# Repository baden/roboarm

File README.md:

## Налаштування оточення

```bash
uv venv --python 3.12
source .venv/bin/activate
uv pip install matplotlib
uv pip install shapely
```

## Візуалізація

```bash
python ./test1.py
```

```bash
python ./pyplot_cycloid1.py
```

## Друге коліно.

Шось позаписую.
Зібрано прототип на базі

Шо я бачу. Шо 1:23 явно для 3Д друку - це перебір.
Зміщення +-1.0 замало, бажано раза в півтора підняти.

- зовнішнього підшипника 52х40х7
- внутрішнього підшипника спочатку на 8х22х7, потім замінено на 10х19х5

Шо я бачу.
Внутрішній треба спробувати всунути 15х24х5, для зміцнення валу

## База

Базу пропоную проєктувати на базі автомобільної ступіци.
Мені здається шо це може бути найпростіший, та мабуть найдешевний варіант.
Треба шоб конструкція витримувала навантаження на ізлом, мала б надійне кріплення до кузова.

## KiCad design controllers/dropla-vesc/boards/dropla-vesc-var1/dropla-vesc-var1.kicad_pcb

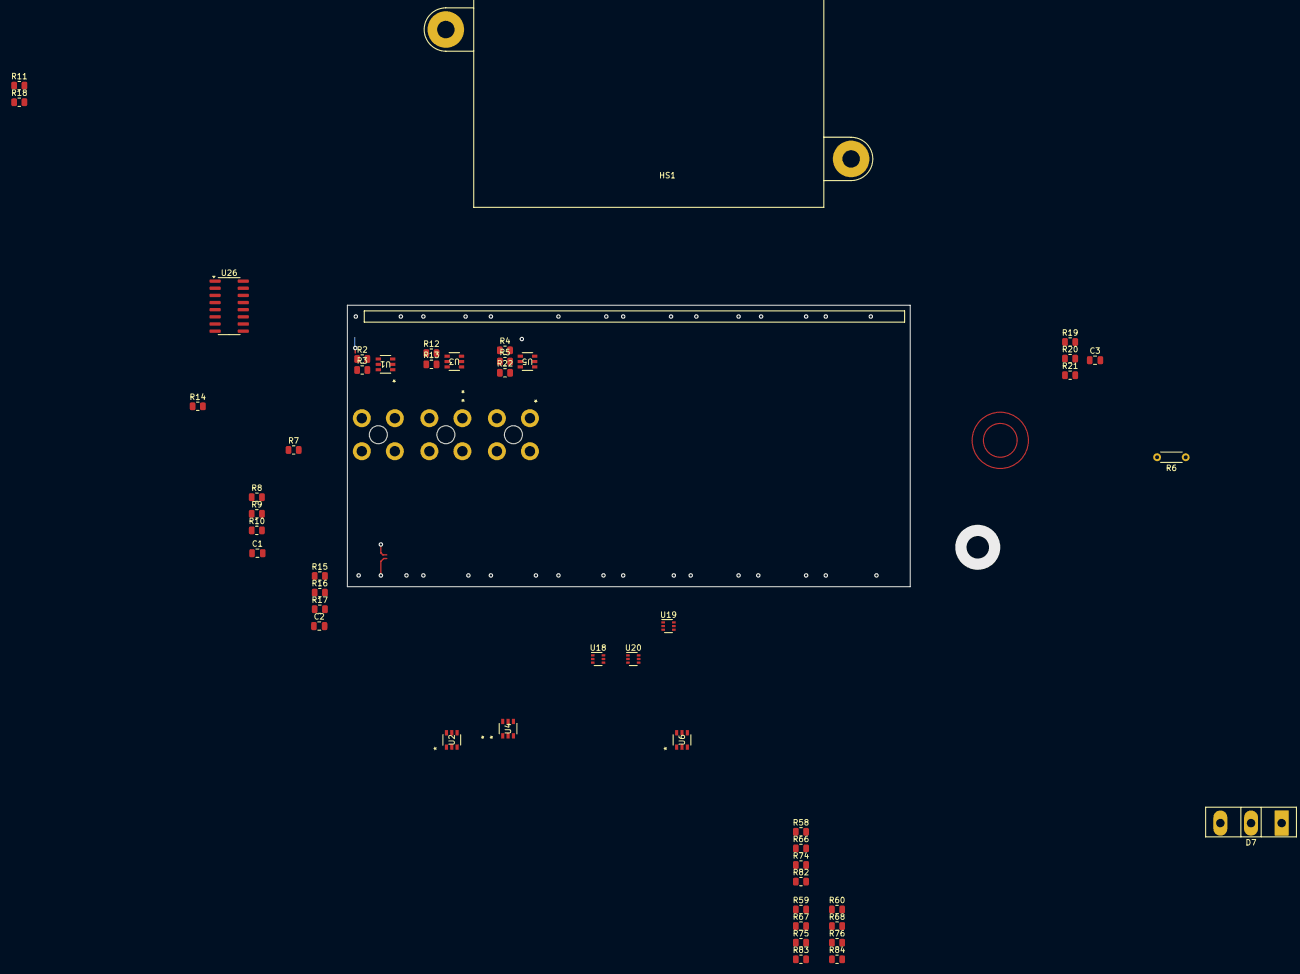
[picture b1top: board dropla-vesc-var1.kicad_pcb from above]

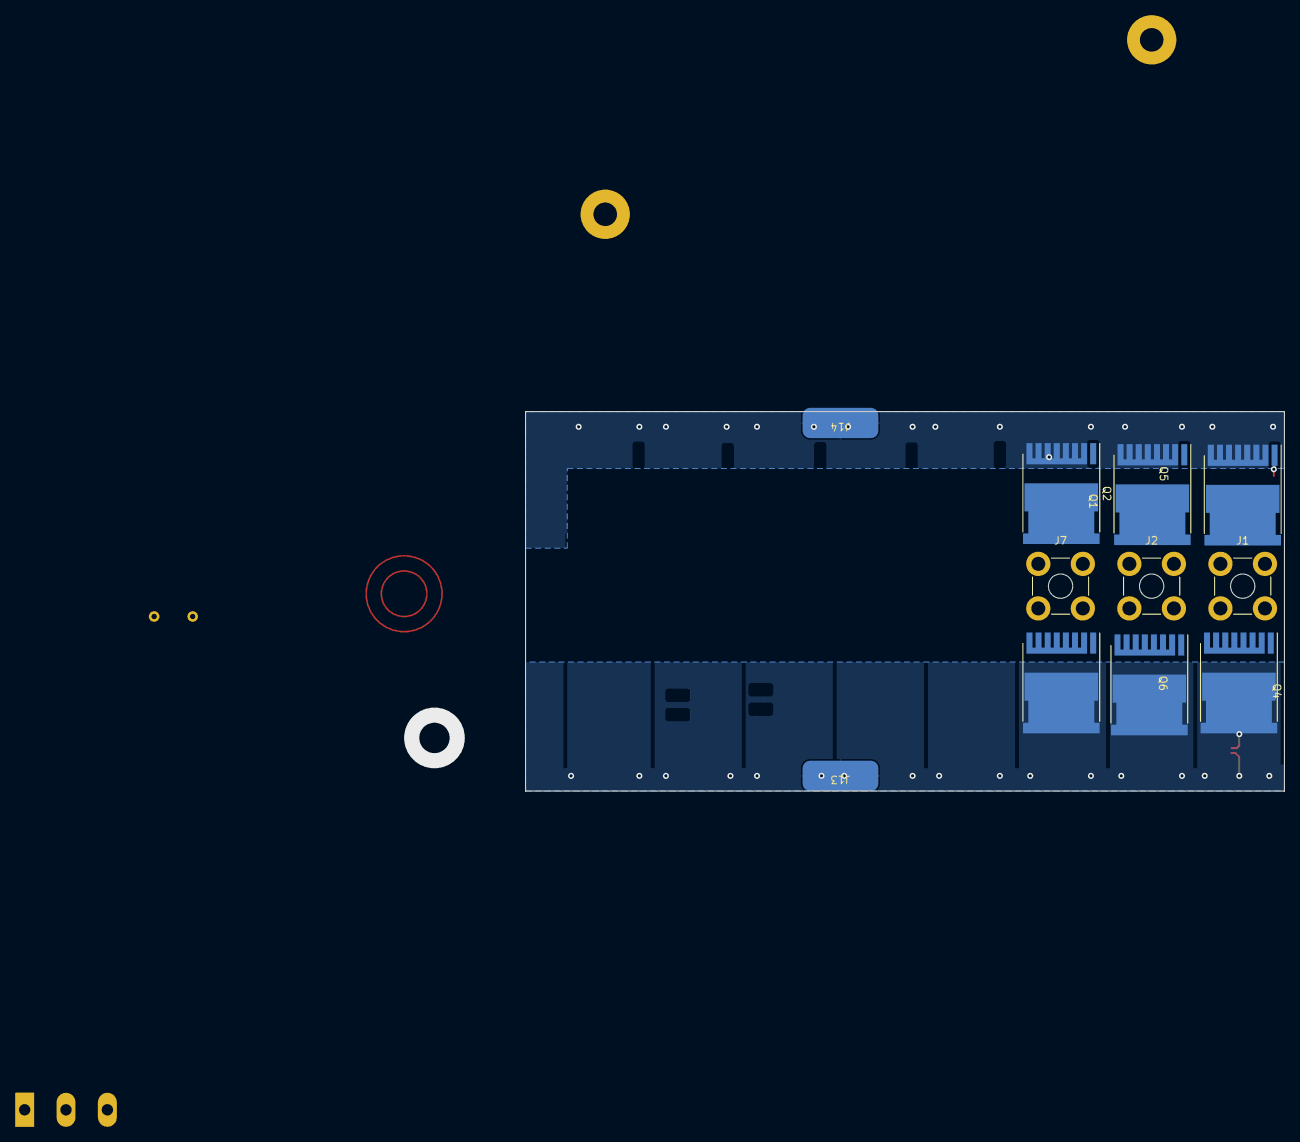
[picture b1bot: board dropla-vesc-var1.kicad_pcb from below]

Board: 2 copper layers, 100.0 x 50.0 mm, 59 parts (11 on the bottom side), 44 nets.

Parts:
C1, C2, C3: C; C_0805_2012Metric
D7: FEP30JP-E3/45; TO-247-3_Vertical
HS1: Heatsink; Heatsink_62x40mm_2xFixation3mm
J1, J2, J7: Screw_Terminal_01x01; Wuerth_REDCUBE-THR_WP-THRBU_74650073_THR
J13, J14: Screw_Terminal_01x01; copper_p_plate
Q1, Q2, Q3, Q4, Q5, Q6: IRFP4110PBF; Infineon_PG-HSOF-8-1
R2, R4, R7, R12, R14, R19: 10; R_0805_2012Metric
R3, R5, R8, R13, R15, R20: 47; R_0805_2012Metric
R6: 1k; R_Axial_DIN0204_L3.6mm_D1.6mm_P5.08mm_Horizontal
R9, R10, R11, R16, R17, R18, R21, R22, R58, R59, R60, R66, R67, R68, R74, R75, R76, R82, R83, R84: 10k; R_0805_2012Metric
U1, U2, U3, U4, U5, U6: 1EDN6550BXTSA1; PG-SOT23-6_INF
U18, U19, U20: NCS211; SOT-363_SC-70-6
U26: CH32V003AxMx; SOP-16_3.9x9.9mm_P1.27mm

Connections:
12V: U2.4 (VDD), U4.4 (VDD), U6.4 (VDD), U18.3 (Vs), U19.3 (Vs), U20.3 (Vs)
+36V: J14.1, Q1.2 (D), Q2.2 (D), Q5.2 (D)
/P1A: C1.2, J1.1, Q1.3 (S), Q4.2 (D), R10.2, U1.2 (GND)
/P1B: C2.2, J2.1, Q5.3 (S), Q6.2 (D), R17.2, U3.2 (GND)
/P2A: C3.2, J7.1, Q2.3 (S), Q3.2 (D), R22.2, U5.2 (GND)
/SCL: R18.1, U26.2 (PC2)
/SDA: R11.1, U26.1 (PC1)
/driver 1A/PWM1: R58.1, R82.1
/driver 1A/PWM2: R66.1, R74.1
/driver 1B/PWM1: R59.1, R83.1
/driver 1B/PWM2: R67.1, R75.1
/driver 2A/PWM1: R60.1, R84.1
/driver 2A/PWM2: R68.1, R76.1
GND: J13.1, Q3.3 (S), Q4.3 (S), Q6.3 (S), R9.2, R16.2, R21.2, U2.2 (GND), U4.2 (GND), U6.2 (GND), U18.2 (GND), U18.4 (+IN), U18.5 (-IN), U19.2 (GND), U19.4 (+IN), U19.5 (-IN), U20.2 (GND), U20.4 (+IN), U20.5 (-IN)
unnamed: C1.1, R2.2, U1.4 (VDD), U1.6 (OUT_SNK)
unnamed: C2.1, R12.2, U3.4 (VDD), U3.6 (OUT_SNK)
unnamed: C3.1, R4.2, U5.4 (VDD), U5.6 (OUT_SNK)
unnamed: Q1.1 (G), R2.1, R3.1, R10.1
unnamed: Q2.1 (G), R4.1, R5.1, R22.1
unnamed: Q3.1 (G), R19.1, R20.1, R21.1
unnamed: Q4.1 (G), R7.1, R8.1, R9.1
unnamed: Q5.1 (G), R12.1, R13.1, R17.1
unnamed: Q6.1 (G), R14.1, R15.1, R16.1
unnamed: R66.2, U1.3 (IN+)
unnamed: R58.2, U1.1 (IN-)
unnamed: R3.2, U1.5 (OUT_SRC)
unnamed: R82.2, U2.3 (IN+)
unnamed: R74.2, U2.1 (IN-)
unnamed: R7.2, U2.6 (OUT_SNK)
unnamed: R8.2, U2.5 (OUT_SRC)
unnamed: R67.2, U3.3 (IN+)
unnamed: R59.2, U3.1 (IN-)
unnamed: R13.2, U3.5 (OUT_SRC)
unnamed: R83.2, U4.3 (IN+)
unnamed: R75.2, U4.1 (IN-)
unnamed: R14.2, U4.6 (OUT_SNK)
unnamed: R15.2, U4.5 (OUT_SRC)
unnamed: R68.2, U5.3 (IN+)
unnamed: R60.2, U5.1 (IN-)
unnamed: R5.2, U5.5 (OUT_SRC)
unnamed: R84.2, U6.3 (IN+)
unnamed: R76.2, U6.1 (IN-)
unnamed: R19.2, U6.6 (OUT_SNK)
unnamed: R20.2, U6.5 (OUT_SRC)

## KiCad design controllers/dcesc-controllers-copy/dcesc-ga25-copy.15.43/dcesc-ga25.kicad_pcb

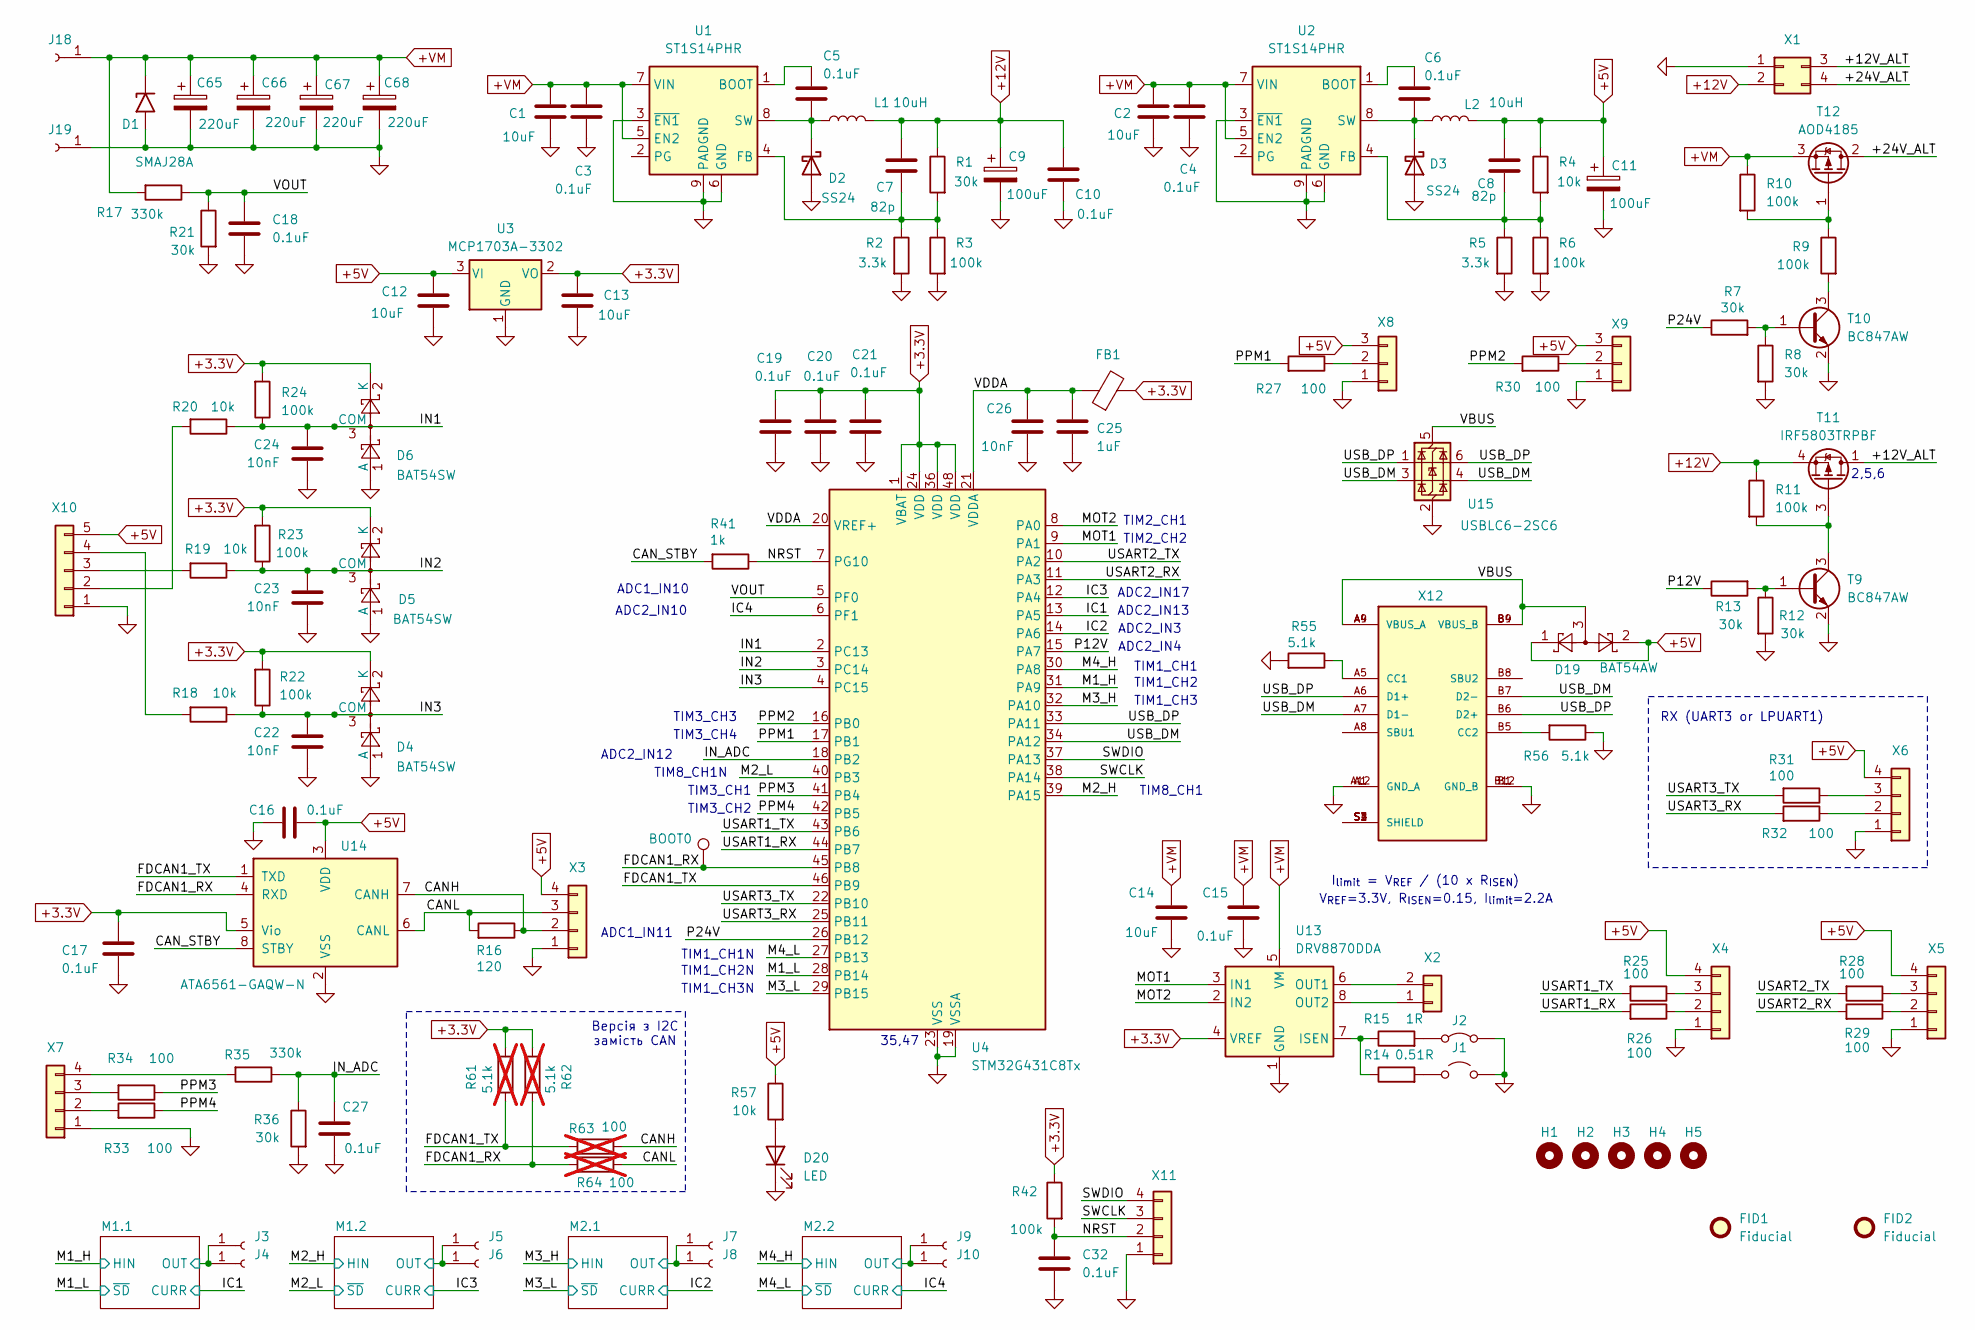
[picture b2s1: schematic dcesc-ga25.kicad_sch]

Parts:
C1, C2, C14: 10uF; C_1206_3216Metric
C3, C4, C5, C6, C10, C15, C16, C17, C18, C19, C20, C21, C27, C32: 0.1uF; C_0603_1608Metric
C7, C8: 82p; C_0603_1608Metric
C9: 100uF; CP_EIA-7343-15_Kemet-W
C11: 100uF; CP_EIA-3528-12_Kemet-T
C12, C13: 10uF; C_0805_2012Metric
C22, C23, C24, C26: 10nF; C_0603_1608Metric
C25: 1uF; C_0603_1608Metric
C65, C66, C67, C68: 220uF; CP_Radial_D10.0mm_P5.00mm
D1: SMAJ28A; D_SMA
D2, D3: SS24; D_SMA
D4, D5, D6: BAT54SW; SOT-323_SC-70
D19: BAT54AW; SOT-323_SC-70
D20: LED; LED_0805_2012Metric
FB1: FerriteBead; L_0603_1608Metric
FID1, FID2: Fiducial; Fiducial_1mm_Mask2mm
H1, H2, H3, H4, H5: MountingHole; MountingHole_3.2mm_M3
J1: Jumper_2_Open; SolderJumper-2_P1.3mm_Open_RoundedPad1.0x1.5mm
J2: Jumper_2_Bridged; SolderJumper-2_P1.3mm_Bridged_RoundedPad1.0x1.5mm
J3, J4, J5, J6, J7, J8, J9, J10: Conn_01x01_Socket; SolderWire-2.5sqmm_1x01_D2.4mm_OD4.4mm
J18, J19: Conn_01x01_Socket; SolderWire-6sqmm_1x01_D3.5mm_OD7mm
L1, L2: 10uH; Inductor_NR6028T100M
R1, R7, R8, R12, R13, R21, R36: 30k; R_0603_1608Metric
R2, R5: 3.3k; R_0603_1608Metric
R3, R6, R9, R10, R11, R22, R23, R24, R42: 100k; R_0603_1608Metric
R4, R18, R19, R20, R57: 10k; R_0603_1608Metric
R14: 0.51R; R_1206_3216Metric
R15: 1R; R_1206_3216Metric
R16: 120; R_0603_1608Metric
R17, R35: 330k; R_0603_1608Metric
R25, R26, R27, R28, R29, R30, R31, R32, R33, R34: 100; R_0603_1608Metric
R41: 1k; R_0603_1608Metric
R55, R56: 5.1k; R_0603_1608Metric
R61, R62: 5.1k; R_0603_1608Metric; not fitted
R63, R64: 100; R_0603_1608Metric; not fitted
T9, T10: BC847AW; SOT-323_SC-70
T11: IRF5803TRPBF; TSOP-6_1.65x3.05mm_P0.95mm
T12: AOD4185; TO-252-2
TP1: BOOT0; TestPoint_Pad_1.0x1.0mm
U1, U2: ST1S14PHR; TI_SO-PowerPAD-8
U3: MCP1703A-3302; MCP1703; MPN MCP1703T-3302E/CB
U4: STM32G431C8Tx; LQFP-48_7x7mm_P0.5mm
U13: DRV8870DDA; Texas_HTSOP-8-1EP_3.9x4.9mm_P1.27mm_EP2.95x4.9mm_Mask2.4x3.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
U14: ATA6561-GAQW-N; SOIC-8_3.9x4.9mm_P1.27mm
U15: USBLC6-2SC6; SOT-23-6
X1: Conn_02x02_Top_Bottom; Molex_Micro-Fit_3.0_43045-0412_2x02_P3.00mm_Vertical
X2: Conn_01x03; JST_XH_B2B-XH-AM_1x02_P2.50mm_Vertical
X3, X4, X5, X6, X7, X11: Conn_01x03; JST_ZH_B4B-ZR_1x04_P1.50mm_Vertical
X8, X9: Conn_01x03; JST_ZH_B3B-ZR_1x03_P1.50mm_Vertical
X10: Conn_01x03; JST_ZH_B5B-ZR_1x05_P1.50mm_Vertical
X12: USB4120-03-C_REVA; GCT_USB4120-03-C_REVA; PARTREV A

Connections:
+3.3V: C13.1, C17.1, C19.1, C20.1, C21.1, D4.2 (K), D5.2 (K), D6.2 (K), FB1.2, R22.2, R23.2, R24.2, R42.1, R61.1, R62.1, U3.2 (VO), U4.1 (VBAT), U4.24 (VDD), U4.36 (VDD), U4.48 (VDD), U13.4 (VREF), U14.5 (Vio); also elsewhere on the board
+5V: C8.1, C11.1, C12.1, C16.1, D19.1, D19.2, L2.2, R4.1, R57.1, U3.3 (VI), U14.3 (VDD), X3.4, X4.4, X5.4, X6.4, X8.3, X9.3, X10.5
+12V: C7.1, C9.1, C10.1, L1.2, R1.1, R11.1, T11.4 (S), X1.2; also elsewhere on the board
+VM: C1.1, C2.1, C3.1, C4.1, C14.1, C15.1, C65.1, C66.1, C67.1, C68.1, D1.1 (A1), J18.1, R10.1, R17.2, T12.3 (S), U1.5 (EN2), U1.7 (VIN), U2.5 (EN2), U2.7 (VIN), U13.5 (VM); also elsewhere on the board
/+12V_ALT: T11.1 (D), T11.2 (D), T11.5 (D), T11.6 (D), X1.3
/+24V_ALT: T12.2 (D), X1.4
/CANH: R16.1, R63.2, U14.7 (CANH), X3.2
/CANL: R16.2, R64.1, U14.6 (CANL), X3.3
/CAN_STBY: R41.2, U14.8 (STBY)
/FDCAN1_RX: R62.2, R64.2, TP1.1, U4.45 (PB8), U14.4 (RXD)
/FDCAN1_TX: R61.2, R63.1, U4.46 (PB9), U14.1 (TXD)
/IC1: U4.13 (PA5); also elsewhere on the board
/IC2: U4.14 (PA6); also elsewhere on the board
/IC3: U4.12 (PA4); also elsewhere on the board
/IC4: U4.6 (PF1); also elsewhere on the board
/IN1: C24.1, D6.3 (COM), R20.1, R24.1, U4.2 (PC13)
/IN2: C23.1, D5.3 (COM), R19.1, R23.1, U4.3 (PC14)
/IN3: C22.1, D4.3 (COM), R18.1, R22.1, U4.4 (PC15)
/IN_ADC: C27.1, R35.1, R36.1, U4.18 (PB2)
/M1.1/OUT: J3.1, J4.1; also elsewhere on the board
/M1.2/OUT: J5.1, J6.1; also elsewhere on the board
/M1_H: U4.31 (PA9); also elsewhere on the board
/M1_L: U4.28 (PB14); also elsewhere on the board
/M2.1/OUT: J7.1, J8.1; also elsewhere on the board
/M2.2/OUT: J9.1, J10.1; also elsewhere on the board
/M2_H: U4.39 (PA15); also elsewhere on the board
/M2_L: U4.40 (PB3); also elsewhere on the board
/M3_H: U4.32 (PA10); also elsewhere on the board
/M3_L: U4.29 (PB15); also elsewhere on the board
/M4_H: U4.30 (PA8); also elsewhere on the board
/M4_L: U4.27 (PB13); also elsewhere on the board
/MOT1: U4.9 (PA1), U13.3 (IN1)
/MOT2: U4.8 (PA0), U13.2 (IN2)
/NRST: C32.1, R41.1, R42.2, U4.7 (PG10), X11.2
/P12V: R13.1, U4.15 (PA7)
/P24V: R7.1, U4.26 (PB12)
/PPM1: R27.2, U4.17 (PB1)
/PPM2: R30.2, U4.16 (PB0)
/PPM3: R34.1, U4.41 (PB4)
/PPM4: R33.1, U4.42 (PB5)
/SWCLK: U4.38 (PA14), X11.3
/SWDIO: U4.37 (PA13), X11.4
/USART1_RX: R26.2, U4.44 (PB7)
/USART1_TX: R25.2, U4.43 (PB6)
/USART2_RX: R29.2, U4.11 (PA3)
/USART2_TX: R28.2, U4.10 (PA2)
/USART3_RX: R32.2, U4.25 (PB11)
/USART3_TX: R31.2, U4.22 (PB10)
/USB_DM: U4.34 (PA12), U15.3 (I/O2), U15.4 (I/O2), X12.A7 (D1-), X12.B7 (D2-)
/USB_DP: U4.33 (PA11), U15.1 (I/O1), U15.6 (I/O1), X12.A6 (D1+), X12.B6 (D2+)
/VBUS: D19.3, U15.5 (VBUS), X12.A4 (VBUS_A), X12.A9 (VBUS_A), X12.B4 (VBUS_B), X12.B9 (VBUS_B)
/VDDA: C25.1, C26.1, FB1.1, U4.20 (VREF+), U4.21 (VDDA)
/VOUT: C18.1, R17.1, R21.1, U4.5 (PF0)
GND: C1.2, C2.2, C3.2, C4.2, C9.2, C10.2, C11.2, C12.2, C13.2, C14.2, C15.2, C16.2, C17.2, C18.2, C19.2, C20.2, C21.2, C22.2, C23.2, C24.2, C25.2, C26.2, C27.2, C32.2, C65.2, C66.2, C67.2, C68.2, D1.2 (A2), D2.2 (A), D3.2 (A), D4.1 (A), D5.1 (A), D6.1 (A), D20.1 (K), J1.2 (B), J2.2 (B), J19.1, R2.2, R3.2, R5.2, R6.2, R8.2, R12.2, R21.2, R36.2, R55.2, R56.1, T9.2 (E), T10.2 (E), U1.3 (~EN1), U1.6 (GND), U1.9 (PADGND), U2.3 (~EN1), U2.6 (GND), U2.9 (PADGND), U3.1 (GND), U4.19 (VSSA), U4.23 (VSS), U4.35 (VSS), U4.47 (VSS), U13.1 (GND), U13.9 (GND), U14.2 (VSS), U15.2 (GND), X1.1, X3.1, X4.1, X5.1, X6.1, X7.1, X8.1, X9.1, X10.1, X11.1, X12.A1 (GND_A), X12.A12 (GND_A), X12.B1 (GND_B), X12.B12 (GND_B); also elsewhere on the board
unnamed: C5.2, D2.1 (K), L1.1, U1.8 (SW)
unnamed: C6.2, D3.1 (K), L2.1, U2.8 (SW)
unnamed: D20.2 (A), R57.2
unnamed: J1.1 (A), R14.2
unnamed: J2.1 (A), R15.2
unnamed: R12.1, R13.2, T9.1 (B)
unnamed: R7.2, R8.1, T10.1 (B)
unnamed: R9.2, T10.3 (C)
unnamed: R11.2, T9.3 (C), T11.3 (G)
unnamed: R9.1, R10.2, T12.1 (G)
unnamed: C5.1, U1.1 (BOOT)
unnamed: C7.2, R1.2, R2.1, R3.1, U1.4 (FB)
unnamed: C6.1, U2.1 (BOOT)
unnamed: C8.2, R4.2, R5.1, R6.1, U2.4 (FB)
unnamed: R14.1, R15.1, U13.7 (ISEN)
unnamed: U13.6 (OUT1), X2.2
unnamed: U13.8 (OUT2), X2.1
unnamed: R26.1, X4.2
unnamed: R25.1, X4.3
unnamed: R29.1, X5.2
unnamed: R28.1, X5.3
unnamed: R32.1, X6.2
unnamed: R31.1, X6.3
unnamed: R33.2, X7.2
unnamed: R34.2, X7.3
unnamed: R35.2, X7.4
unnamed: R27.1, X8.2
unnamed: R30.1, X9.2
unnamed: R20.2, X10.2
unnamed: R19.2, X10.3
unnamed: R18.2, X10.4
unnamed: R55.1, X12.A5 (CC1)
unnamed: R56.2, X12.B5 (CC2)
unnamed: X12.S1 (SHIELD), X12.S2 (SHIELD), X12.S3 (SHIELD), X12.S4 (SHIELD)

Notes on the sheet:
TIM1_CH2N
TIM1_CH2
TIM3_CH1
ADC2_IN13
Версія з I2C замість CAN
TIM1_CH1
2,5,6
ADC1_IN10
TIM8_CH1
TIM1_CH1N
TIM3_CH4
ADC2_IN12
TIM3_CH3
RX (UART3 or LPUART1)
ADC1_IN11
I_{limit} = V_{REF} / (10 x R_{ISEN})
TIM1_CH3
TIM1_CH3N
V_{REF}=3.3V, R_{ISEN}=0.15, I_{limit}=2.2A
ADC2_IN17
TIM8_CH1N
TIM3_CH2
ADC2_IN4
ADC2_IN3
TIM2_CH2
ADC2_IN10
35,47
TIM2_CH1

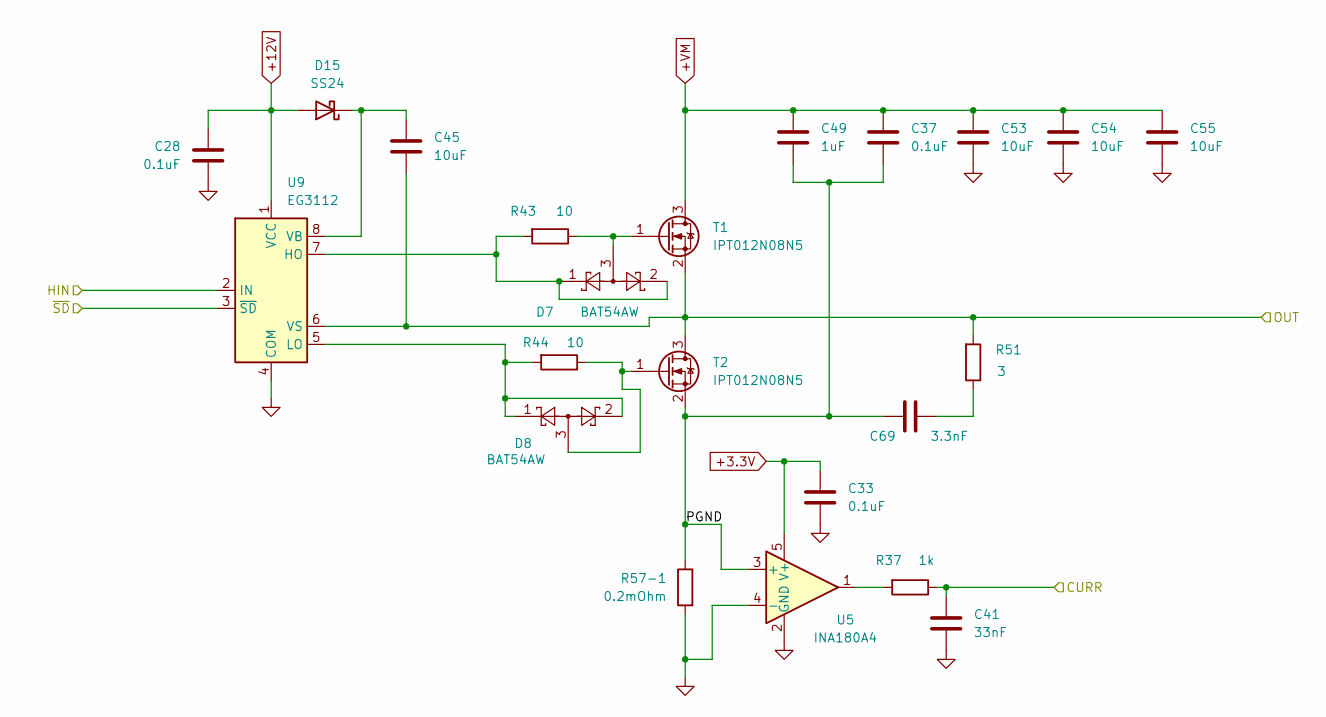
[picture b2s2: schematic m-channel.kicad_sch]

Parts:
C28, C33, C37: 0.1uF; C_0603_1608Metric
C41: 33nF; C_0603_1608Metric
C45: 10uF; C_0805_2012Metric
C49: 1uF; C_0805_2012Metric
C53, C54, C55: 10uF; C_1206_3216Metric
C69: 3.3nF; C_0603_1608Metric
D7, D8: BAT54AW; SOT-323_SC-70
D15: SS24; D_SMA
R37: 1k; R_0603_1608Metric
R43, R44: 10; R_0603_1608Metric
R51: 3; R_1206_3216Metric
R57-1: 0.2mOhm; R_SHUNT
T1, T2: IPT012N08N5; Infineon_PG-HSOF-8-1
U5: INA180A4; SOT-23-5
U9: EG3112; SOP-8_3.9x4.9mm_P1.27mm

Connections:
+3.3V: C33.1, U5.5 (V+); also elsewhere on the board
+12V: C28.1, D15.2 (A), U9.1 (VCC); also elsewhere on the board
+VM: C37.1, C49.1, C53.1, C54.1, C55.1, T1.3 (D); also elsewhere on the board
/IC1: C41.1, R37.1; also elsewhere on the board
/M1.1/OUT: C45.2, R51.2, T1.2 (S), T2.3 (D), U9.6 (VS); also elsewhere on the board
/M1.1/PGND: C37.2, C49.2, C69.2, R57-1.1, T2.2 (S), U5.3 (+)
/M1_H: U9.2 (IN); also elsewhere on the board
/M1_L: U9.3 (~SD); also elsewhere on the board
GND: C28.2, C33.2, C41.2, C53.2, C54.2, C55.2, R57-1.2, U5.2 (GND), U5.4 (-), U9.4 (COM); also elsewhere on the board
unnamed: C69.1, R51.1
unnamed: C45.1, D15.1 (K), U9.8 (VB)
unnamed: R37.2, U5.1
unnamed: D7.3, R43.1, T1.1 (G)
unnamed: D8.3, R44.1, T2.1 (G)
unnamed: D7.1, D7.2, R43.2, U9.7 (HO)
unnamed: D8.1, D8.2, R44.2, U9.5 (LO)

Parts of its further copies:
C29, C30, C31, C34, C35, C36, C38, C39, C40: 0.1uF; C_0603_1608Metric
C42, C43, C44: 33nF; C_0603_1608Metric
C46, C47, C48: 10uF; C_0805_2012Metric
C50, C51, C52: 1uF; C_0805_2012Metric
C56, C57, C58, C59, C60, C61, C62, C63, C64: 10uF; C_1206_3216Metric
C70, C71, C72: 3.3nF; C_0603_1608Metric
D9, D10, D11, D12, D13, D14: BAT54AW; SOT-323_SC-70
D16, D17, D18: SS24; D_SMA
R38, R39, R40: 1k; R_0603_1608Metric
R45, R46, R47, R48, R49, R50: 10; R_0603_1608Metric
R52, R53, R54: 3; R_1206_3216Metric
R58-1, R59-1, R60-1: 0.2mOhm; R_SHUNT
T3, T4, T5, T6, T7, T8: IPT012N08N5; Infineon_PG-HSOF-8-1
U6, U7, U8: INA180A4; SOT-23-5
U10, U11, U12: EG3112; SOP-8_3.9x4.9mm_P1.27mm

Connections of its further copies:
+3.3V: C34.1, C35.1, C36.1, U6.5 (V+), U7.5 (V+), U8.5 (V+); also elsewhere on the board
+12V: C29.1, C30.1, C31.1, D16.2 (A), D17.2 (A), D18.2 (A), U10.1 (VCC), U11.1 (VCC), U12.1 (VCC); also elsewhere on the board
+VM: C38.1, C39.1, C40.1, C50.1, C51.1, C52.1, C56.1, C57.1, C58.1, C59.1, C60.1, C61.1, C62.1, C63.1, C64.1, T3.3 (D), T5.3 (D), T7.3 (D); also elsewhere on the board
/IC2: C43.1, R39.1; also elsewhere on the board
/IC3: C42.1, R38.1; also elsewhere on the board
/IC4: C44.1, R40.1; also elsewhere on the board
/M1.2/OUT: C46.2, R52.2, T3.2 (S), T4.3 (D), U10.6 (VS); also elsewhere on the board
/M1.2/PGND: C38.2, C50.2, C70.2, R59-1.1, T4.2 (S), U6.3 (+)
/M2.1/OUT: C47.2, R53.2, T5.2 (S), T6.3 (D), U11.6 (VS); also elsewhere on the board
/M2.1/PGND: C39.2, C51.2, C71.2, R58-1.1, T6.2 (S), U7.3 (+)
/M2.2/OUT: C48.2, R54.2, T7.2 (S), T8.3 (D), U12.6 (VS); also elsewhere on the board
/M2.2/PGND: C40.2, C52.2, C72.2, R60-1.1, T8.2 (S), U8.3 (+)
/M2_H: U10.2 (IN); also elsewhere on the board
/M2_L: U10.3 (~SD); also elsewhere on the board
/M3_H: U11.2 (IN); also elsewhere on the board
/M3_L: U11.3 (~SD); also elsewhere on the board
/M4_H: U12.2 (IN); also elsewhere on the board
/M4_L: U12.3 (~SD); also elsewhere on the board
GND: C29.2, C30.2, C31.2, C34.2, C35.2, C36.2, C42.2, C43.2, C44.2, C56.2, C57.2, C58.2, C59.2, C60.2, C61.2, C62.2, C63.2, C64.2, R58-1.2, R59-1.2, R60-1.2, U6.2 (GND), U6.4 (-), U7.2 (GND), U7.4 (-), U8.2 (GND), U8.4 (-), U10.4 (COM), U11.4 (COM), U12.4 (COM); also elsewhere on the board
unnamed: C70.1, R52.1
unnamed: C71.1, R53.1
unnamed: C72.1, R54.1
unnamed: C46.1, D16.1 (K), U10.8 (VB)
unnamed: C47.1, D17.1 (K), U11.8 (VB)
unnamed: C48.1, D18.1 (K), U12.8 (VB)
unnamed: R38.2, U6.1
unnamed: R39.2, U7.1
unnamed: R40.2, U8.1
unnamed: D9.3, R45.1, T3.1 (G)
unnamed: D10.3, R46.1, T4.1 (G)
unnamed: D11.3, R47.1, T5.1 (G)
unnamed: D12.3, R48.1, T6.1 (G)
unnamed: D13.3, R49.1, T7.1 (G)
unnamed: D14.3, R50.1, T8.1 (G)
unnamed: D9.1, D9.2, R45.2, U10.7 (HO)
unnamed: D10.1, D10.2, R46.2, U10.5 (LO)
unnamed: D11.1, D11.2, R47.2, U11.7 (HO)
unnamed: D12.1, D12.2, R48.2, U11.5 (LO)
unnamed: D13.1, D13.2, R49.2, U12.7 (HO)
unnamed: D14.1, D14.2, R50.2, U12.5 (LO)

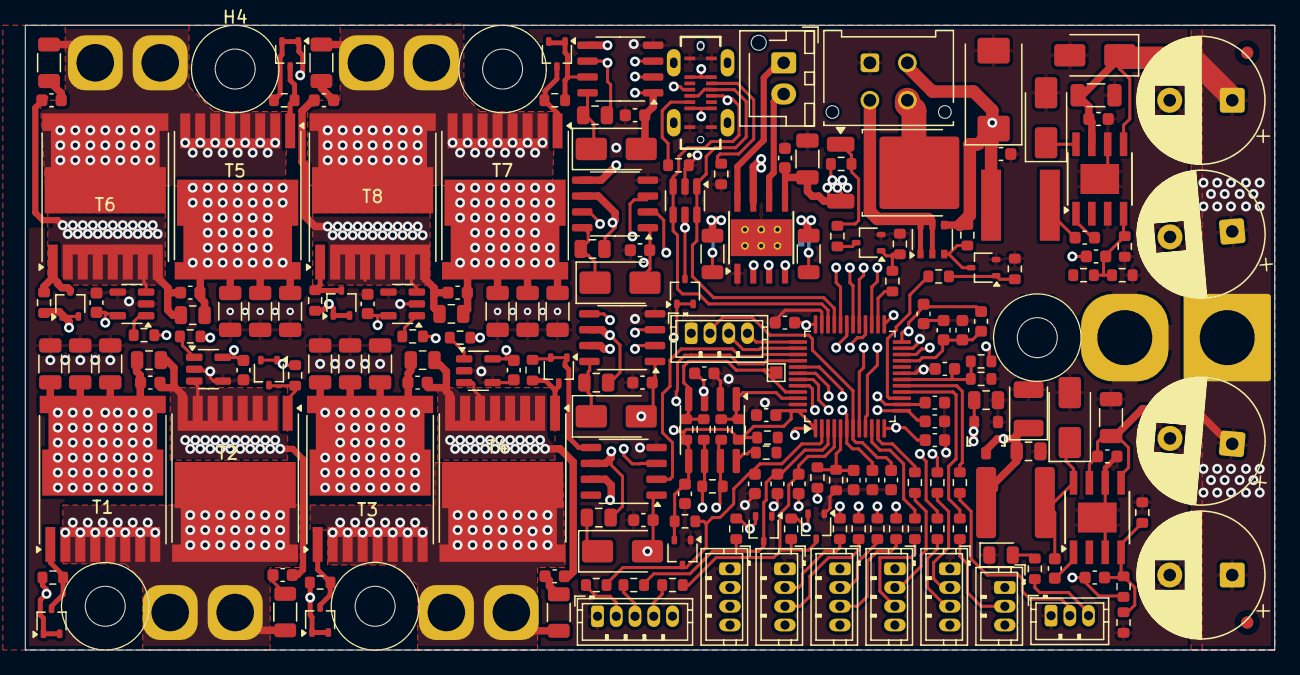
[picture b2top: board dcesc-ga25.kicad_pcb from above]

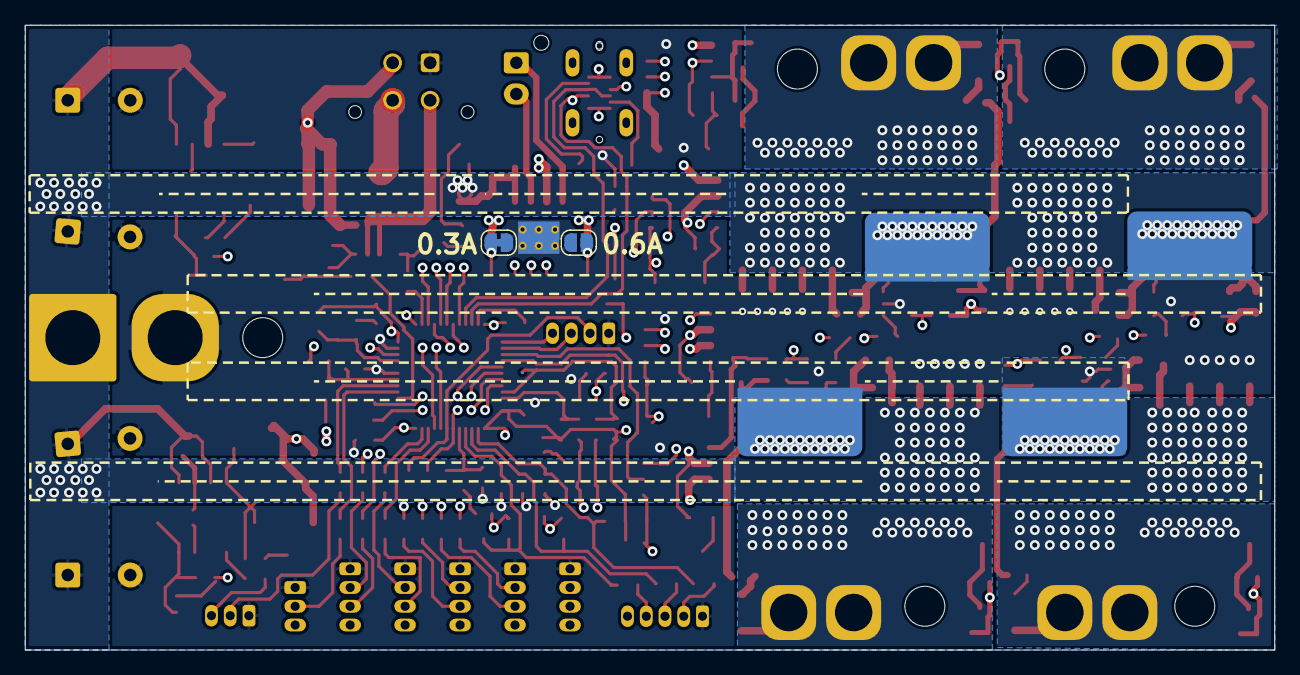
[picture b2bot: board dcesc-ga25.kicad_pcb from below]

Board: 4 copper layers, 100.0 x 50.0 mm, 219 parts (6 on the bottom side), 120 nets.

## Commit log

2024-11-07 nothing
2025-03-13 Спроба запушити Freecad проєкт.
2025-04-24 Updated python files.
2025-06-20 Save it.
2025-06-22 Поступово переходимо на 33-80-4.
2025-06-25 Все ж хочу трохи роздвинути трубки. Та додати підшипники.
2025-08-15 Збереження.
